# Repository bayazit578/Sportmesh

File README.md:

# Sportmesh

## Описание проекта
Cистема КП для спортивного ориентирования, трейлов с возможностью мониторинга участников соревнований в реальном времени на основе кастомной mesh-сети

<<<<<<< HEAD

=======

>>>>>>> dda294a705e08b0016b4b325d384afd2ebc7e439

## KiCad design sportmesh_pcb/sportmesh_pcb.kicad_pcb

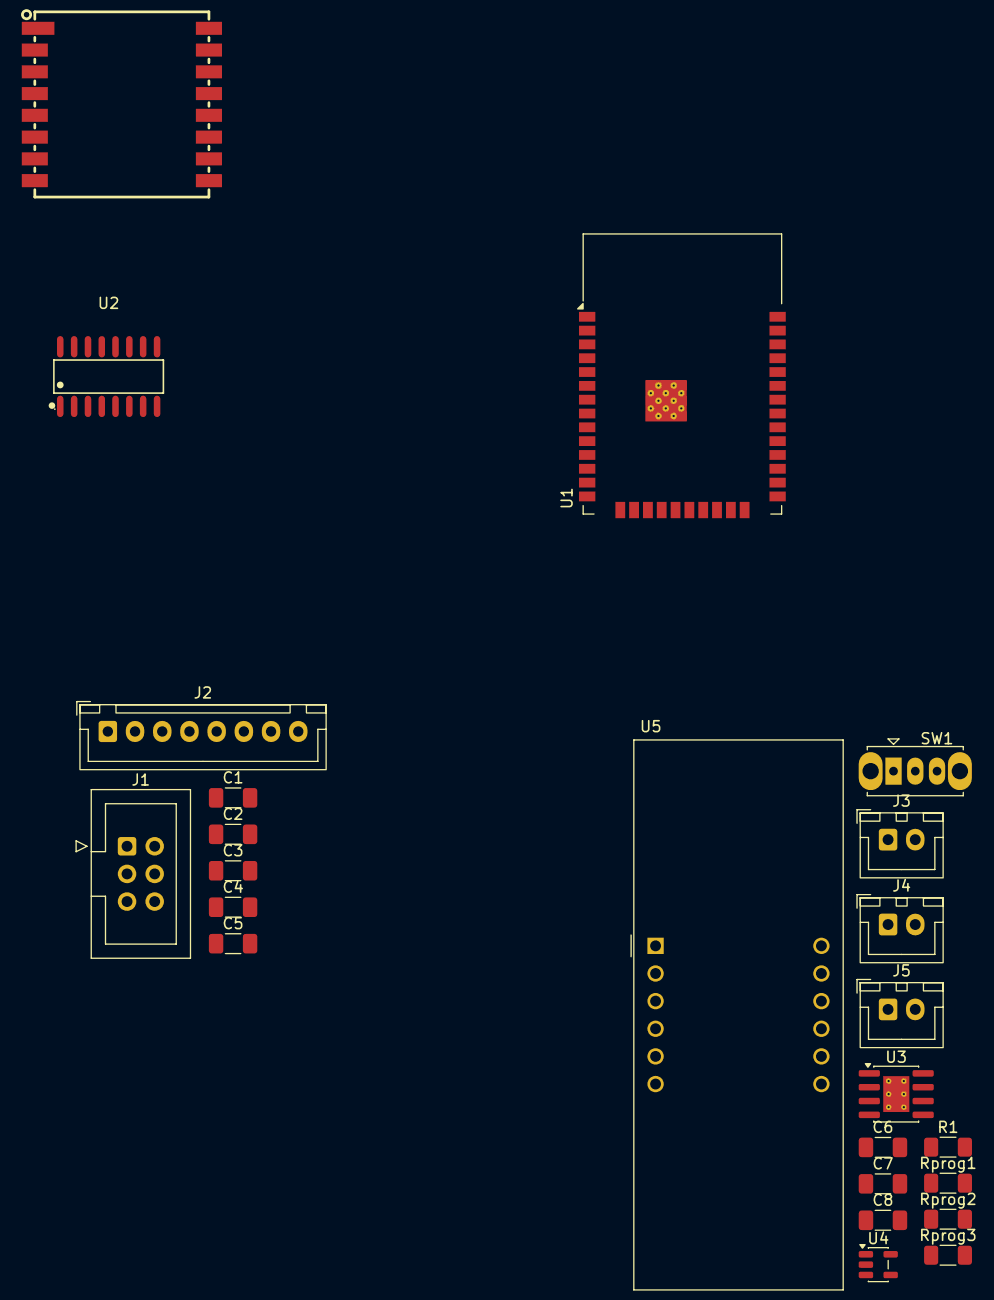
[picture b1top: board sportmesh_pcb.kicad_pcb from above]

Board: 2 copper layers, 24 parts (0 on the bottom side), 27 nets, no tracks yet.

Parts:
C1, C2, C4, C6: 10uF; C_1206_3216Metric_Pad1.33x1.80mm_HandSolder
C3, C5: 0.1uF; C_1206_3216Metric_Pad1.33x1.80mm_HandSolder
C7, C8: 1uF; C_1206_3216Metric_Pad1.33x1.80mm_HandSolder
J1: Conn_02x03_Odd_Even; IDC-Header_2x03_P2.54mm_Vertical
J2: Conn_01x08_Socket; JST_XH_B8B-XH-A_1x08_P2.50mm_Vertical
J3, J4, J5: Conn_01x02_Pin; JST_XH_B2B-XH-A_1x02_P2.50mm_Vertical
L1: RA-01SH; WIRELM-SMD_RA-01SH
R1: 1K; R_1206_3216Metric_Pad1.30x1.75mm_HandSolder
Rprog1, Rprog2, Rprog3: 3.3K; R_1206_3216Metric_Pad1.30x1.75mm_HandSolder
SW1: SW_SPDT; SW_Slide_SPDT_Straight_CK_OS102011MS2Q
U1: ESP32-WROOM-32D
U2: TM1650_C18211636; SOIC-16_L9.9-W3.9-P1.27-LS6.0-BL
U3: TP4056-42-ESOP8; SOIC-8-1EP_3.9x4.9mm_P1.27mm_EP2.41x3.3mm_ThermalVias
U4: TLV75733PDBV; SOT-23-5
U5: CC56-12CGKWA; CA56-12CGKWA

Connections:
+3.3V: C8.1, U4.5 (OUT)
+3V3: C1.1, C2.1, C3.1, C4.1, C5.1, J1.1, J1.2, J2.8, L1.3 (3.3V), U1.2 (VDD), U1.3 (EN)
/sportmesh_pcb_1/IO_0: J1.6, U1.25 (IO0)
/sportmesh_pcb_1/IO_5: L1.15 (NSS), U1.29 (IO5)
/sportmesh_pcb_1/IO_12: J2.4, U1.14 (IO12)
/sportmesh_pcb_1/IO_13: J2.3, U1.16 (IO13)
/sportmesh_pcb_1/IO_14: J2.2, U1.13 (IO14)
/sportmesh_pcb_1/IO_15: J2.1, U1.23 (IO15)
/sportmesh_pcb_1/IO_16: L1.4 (RESET), U1.27 (IO16)
/sportmesh_pcb_1/IO_17: L1.10 (BUSY), U1.28 (IO17)
/sportmesh_pcb_1/IO_18: L1.12 (SCK), U1.30 (IO18)
/sportmesh_pcb_1/IO_19: L1.13 (MISO), U1.31 (IO19)
/sportmesh_pcb_1/IO_22: L1.6 (DIO1), U1.36 (IO22)
/sportmesh_pcb_1/IO_23: L1.14 (MOSI), U1.37 (IO23)
/sportmesh_pcb_1/IO_25: J2.7, U1.10 (IO25)
/sportmesh_pcb_1/IO_26: J2.5, U1.11 (IO26)
/sportmesh_pcb_1/IO_RX0: J1.5, U1.34 (RXD0/IO3)
/sportmesh_pcb_1/IO_TX0: J1.3, U1.35 (TXD0/IO1)
/sportmesh_pcb_2/IO_25: Rprog1.2, Rprog2.1
GND: C1.2, C2.2, C3.2, C4.2, C5.2, C6.2, C7.2, C8.2, J1.4, J2.6, J3.1, L1.2 (GND), L1.9 (GND), L1.16 (GND), Rprog2.2, Rprog3.2, U1.1 (GND), U1.15 (GND), U1.38 (GND), U1.39 (GND), U3.1 (TEMP), U3.3 (GND), U4.2 (GND)
unnamed: C6.1, J3.2, R1.2, U3.8 (CE)
unnamed: J4.1, J5.1, R1.1
unnamed: J4.2, U3.6 (~STDBY)
unnamed: J5.2, U3.7 (~CHRG)
unnamed: SW1.2 (B), U3.5 (BAT)
unnamed: C7.1, Rprog1.1, SW1.3 (C), U4.1 (IN), U4.3 (EN)
unnamed: Rprog3.1, U3.2 (PROG)
